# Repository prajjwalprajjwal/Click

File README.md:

# Clicker Project 🎮

Official repository for the Clicker handheld device ecosystem, encompassing production firmware, hardware schematics, PCB designs, CAD enclosure models, automated asset build pipelines, and browser-based WebUSB & WebSerial flashing tools.

---

## 📁 Repository Structure

```text
Click/
├── README.md                          <-- Master documentation and system overview
├── PROJECT_RULES.md                  <-- Protected subsystems, NVS rules & coding freeze
├── CHANGELOG.md                      <-- Comprehensive release history & architecture decisions
├── LICENSE                           <-- CC BY-NC-SA 4.0 International License
├── platformio.ini                    <-- PlatformIO configuration & automated build flags
├── build_release.bat                 <-- 1-Click Interactive firmware release packager
├── run_flasher.bat                   <-- 1-Click Localhost web flasher server runner
├── flash_device.bat                  <-- 1-Click Desktop CLI serial flasher
├── hardware/                         <-- Electrical schematics, 3D mechanical designs & production files
│   ├── Enclosure/                    <-- CAD enclosure assembly and 3D printable parts
│   │   ├── Assem4.SLDASM             <-- SolidWorks master enclosure assembly
│   │   ├── Click 4.SLDPRT            <-- SolidWorks case part model
│   │   ├── Click4_PCB.SLDPRT         <-- SolidWorks PCB envelope reference
│   │   └── STLs/                     <-- Production 3D-printable stereolithography meshes
│   │       ├── Case.STL              <-- Main device housing
│   │       ├── Case for Hook.STL     <-- Device housing with keychain/lanyard loop
│   │       ├── Back Plate w window.STL <-- Back cover with sensor/battery window
│   │       └── Back Plate w Hook.STL   <-- Back cover with keychain anchor
│   ├── PCB/                          <-- KiCad PCB manufacturing & CAD files
│   │   ├── Click4/                   <-- Active production PCBA (Raspberry Pi RP2354A)
│   │   │   ├── Click4.kicad_sch      <-- Production PCBA schematic
│   │   │   ├── Click4.kicad_pcb      <-- 4-layer impedance-controlled PCB layout
│   │   │   ├── Click4.step           <-- 3D MCAD export for enclosure fit check
│   │   │   └── production/           <-- JLCPCB Gerbers, drill files, BOM & CPL
│   │   ├── Click1/                   <-- Legacy prototype KiCad PCB & schematic (ESP32-WROOM-32E)
│   │   └── Resources/                <-- Edge cut DXFs, silkscreen vector artwork & graphics
│   ├── V4 Production Files/          <-- Ready-to-order manufacturing packages
│   │   ├── for JLCPCB.zip            <-- PCBA fabrication & assembly production archive
│   │   └── for JLC3DP.zip            <-- 3D printing enclosure fabrication archive
│   └── vector_designs.ai             <-- Vector graphics & enclosure laser engraving artwork
├── server/                           <-- Cloudflare Worker + D1 Serverless Leaderboard Backend
│   ├── worker.js                     <-- Edge API routes (/api/leaderboard, /api/sync, /api/user)
│   ├── schema.sql                    <-- D1 SQLite schema (devices, global_stats, sync_log)
│   ├── wrangler.toml                 <-- Cloudflare Worker deployment configuration
│   └── README.md                     <-- 3-minute zero-cost deployment guide
├── firmware/                         <-- Modular C++ embedded firmware
│   ├── assets/screens/               <-- 1-bit screen bitmaps & sprites (.png) + README.md
│   ├── scripts/
│   │   ├── pre_build_assets.py       <-- PlatformIO pre-build hook (auto-converts assets)
│   │   ├── convert_assets.py         <-- Converts PNGs to C PROGMEM bitmap headers
│   │   ├── flash.sh                  <-- Flashing utility for macOS / Linux
│   │   └── flash.bat                 <-- Flashing utility for Windows
│   └── src/                          <-- Application source code & applets
│       ├── main.cpp                  <-- Application entry point, serial protocol & registry
│       ├── system/                   <-- Core OS, drivers & power management (untouched by applets)
│       │   ├── Applet.h              <-- Base class interface for all applets
│       │   ├── OSManager.h / .cpp    <-- Applet scheduler & 3-stage sleep lifecycle
│       │   ├── PowerManager.h        <-- 12MHz XOSC sleep, __wfi(), double-click wake & I2C safety
│       │   ├── PinConfig.h           <-- Authoritative pin routing (RP2354A & ESP32)
│       │   ├── Display.h             <-- SSD1306 OLED singleton & 400kHz fast I2C
│       │   ├── InputManager.h / .cpp <-- Debounced button state machine & dual-key readers
│       │   ├── battery.hpp           <-- Non-linear LiPo curve, ADC filter & ETA6003 STAT
│       │   ├── WS2812.h              <-- PIO driver for 2x SK6812 RGB LEDs (GP11 DIN)
│       │   ├── SoundFX.h             <-- Non-blocking audio buzzer driver (GP27)
│       │   ├── HardwareDiagnostics.h / .cpp <-- Interactive & automated hardware test suite
│       │   └── device_info.hpp / .cpp<-- RP2354 Unique Board ID / eFuse MAC & custom bootscreen name
│       ├── applets/                  <-- Self-contained, modular games & apps
│       │   ├── clicker/              <-- Sisyphus uphill clicker game & physics engine
│       │   ├── timing_game/          <-- "Just 10 Seconds" accuracy timing game
│       │   ├── flappy_bird/          <-- Floppy Bird arcade obstacle game
│       │   ├── settings/             <-- Hardware status, voltage & device ID screen
│       │   └── screensaver/          <-- Snowfall particle animation on idle
│       ├── fonts/                    <-- Custom Adafruit GFX typography headers (Rajdhani)
│       ├── screens/                  <-- Legacy milestone overlay renderers
│       └── generated_assets/         <-- Auto-generated C bitmap headers
├── web_flasher/                      <-- WebUSB & WebSerial flasher, personalizer & leaderboard site
│   ├── index.html                    <-- Modern WebUSB/WebSerial application entry point
│   ├── flasher.html                  <-- Full-featured standalone flasher UI
│   ├── app.js                        <-- WebSerial engine, personalization & leaderboard sync
│   ├── rp2350-flash.js               <-- In-browser WebUSB Picoboot flasher & BOOTSEL flow
│   ├── rp2350-flash.css              <-- WebUSB installer & modal responsive styling
│   ├── style.css                     <-- Cyberpunk terminal responsive styling
│   ├── lib/                          <-- In-browser flashing drivers
│   │   ├── picoboot/                 <-- Native WebUSB Picoboot protocol driver (RP2350/RP2354)
│   │   └── uf2.js                    <-- Browser UF2 binary encoder/decoder
│   ├── flash-rp2350.bat / .sh        <-- Desktop Picotool update helper scripts
│   ├── manifest.json                 <-- WebSerial firmware manifest
│   ├── versions.json                 <-- Release catalog with hashes and download links
│   ├── releases/                     <-- Multi-version release archive (v0.1.1, v0.1.0, v0.0.1)
│   └── README.md                     <-- Web flasher guide, WebUSB/WebSerial docs & hosting
├── tools/                            <-- Build & developer utilities
│   ├── release/release_manager.py    <-- Interactive version bumper & binary packager
│   ├── flasher/                      <-- Flasher runner & desktop CLI scripts
│   │   ├── serve_flasher.py          <-- Zero-config HTTP server for web_flasher
│   │   └── flash_device.py           <-- Desktop serial flasher script
│   └── converters/                   <-- TTF font and image conversion scripts
└── docs/                             <-- Architectural specifications
    ├── hardware_and_pinouts.md       <-- Detailed pin profiles (RP2354A vs ESP32)
    ├── power_management_and_battery_architecture.md <-- Power optimization, battery fuel gauging & sleep currents
    ├── device_identification_and_leaderboard.md <-- Unique hardware ID & database schema
    └── leaderboard_architecture.md   <-- Cloudflare Worker API & score sync model
```

---

## ⚡ Hardware Platforms & Pin Profiles

Detailed technical schematics and electrical specifications can be found in [`docs/hardware_and_pinouts.md`](docs/hardware_and_pinouts.md).

> [!NOTE]
> **Active Hardware & Production Platforms**:
> - **Active Production Platform (Click 4 - RP2354A)**: Turnkey PCBA featuring the **Raspberry Pi RP2354A** MCU (Dual Cortex-M33, 512KB RAM, 4MB Flash). Features high-precision calibrated Li-Ion battery telemetry, 12MHz active sleep with $< 1\text{ mA}$ power consumption, dual SK6812 RGB LEDs, piezo sound, and PCF8563 RTC. Active default build environment: `env:rp2354`. Design files in `hardware/PCB/Click4/`.
> - **Legacy Prototype (Click 1 - ESP32-WROOM-32E)**: Hand-assembled prototype board maintained for backward compatibility under `env:esp32doit-devkit-v1`. Design files in `hardware/PCB/Click1/`.
> - **Power & Battery Deep-Dive**: For full architectural documentation on power management, battery discharge modeling, and silicon gotchas, read [**`docs/power_management_and_battery_architecture.md`**](docs/power_management_and_battery_architecture.md).

### Active Production Hardware Specs (Click 4: RP2354A)
- **Microcontroller**: Raspberry Pi RP2354A (Dual Cortex-M33 @ 48MHz, 512KB SRAM, 4MB on-chip Flash)
- **Display & RTC I2C Bus**: `CLICK_I2C = Wire1` (SDA = GP2, SCL = GP3, 400kHz Fast I2C)
- **User Inputs**: MODE = GP0 (Active LOW), ACTION = `BOOTSEL` / `QSPI_SS` (Active LOW)
- **Power & Battery**: STAT = GP1 (Active LOW charging from ETA6003 with 10k pullup), BAT_ADC = GP29 (ADC3 via 100k/100k divider)
- **Audio & Visual**: Buzzer = GP27 (via NPN BJT), RGB LEDs = GP11 (2× SK6812 DIN via PIO)
- **Power Management**: Same-Button Double-Click Wake protection (double-clicking the same key within 500ms), 3-stage sleep profile (8s dim, 15s display off, 30s deep sleep at 12MHz down-clocking $< 1\text{ mA}$), I2C bus preservation (0µA idle)

### Legacy Prototype Specs (Click 1: ESP32-WROOM-32E)
- **Microcontroller**: ESP32-WROOM-32E (Xtensa Dual-Core 240MHz, 4MB Flash)
- **Display I2C**: SDA = GPIO 21, SCL = GPIO 22 (400kHz Fast I2C)
- **User Inputs**: MODE = GPIO 14 (RTC ext0 wake), ACTION = GPIO 32 (RTC ext1 wake)
- **Power & Battery**: STAT = GPIO 33, BAT_ADC = GPIO 35 (100k/100k divider)
- **Sleep States**: Light sleep at 20s (OLED off, I2C pullups held), Deep sleep at 45s (RTC wakeup)

---

## 🕹️ Applet Ecosystem & Gameplay

The firmware features an event-driven `OSManager` hosting four built-in applets and an idle screensaver:

### 1. Sisyphus Clicker (Default Applet)
* **Theme**: Sisyphus rolling his eternal boulder up a steep mountain slope.
* **Dynamics**:
  * **Boulder Physics**: Smooth rotation and position tracking based on player clicks.
  * **Stamina & Fatigue**: Continuous clicking builds fatigue; stopping causes Sisyphus to catch his breath.
  * **Auditory Feedback**: 3 short beeps when the boulder rolls back downhill, with a gentle chime upon hitting bottom. Silent on startup into Sisyphus.
  * **Milestone Celebrations**: Overlay banners and RGB celebration pulses trigger on reaching milestone tiers.
  * **Persistence**: Dual-key NVS backup storage with checksum verification and wear-leveling.

### 2. Just Ten
* Precision stopwatch game challenging players to hold and release the button at exactly **10.0000 seconds**.
* Displays exact millisecond accuracy, tracks personal records, and flashes yellowish LEDs upon stopping.

### 3. Floppy Bird
* Real-time side-scrolling obstacle game featuring obstacle collision detection, velocity physics, and persistent high scores with red LED flash on game over.

### 4. Settings & System Applet
* Accessible by holding the **MODE** button.
* **Page 0 (SYSTEM)**: Shows live battery state (`[CHARGING]`, `[BATTERY]`, `[CHARGED]`), high-precision numerical voltage (`x.xxV`), and a graphical charge bar.
* **Page 1 (SYSTEM INFO)**: Center-aligned hardware telemetry displaying Firmware version, unique Device ID, and MCU specifications.

### 5. Snowfall Screensaver
* Ambient particle simulation that activates automatically when the device remains idle prior to entering sleep.

---

## 🎮 Controls & Navigation Guide

| Action | Control | Description |
|:---|:---|:---|
| **Cycle Applets** | `MODE` Button (Short Press) | Switch between **Clicker**, **Just Ten**, and **Floppy Bird** (click chime plays except before Sisyphus). |
| **Settings Menu** | `MODE` Button (Hold > 1s) | Toggle between the currently active applet and the **SYSTEM** settings screen. |
| **Toggle System Info** | `ACTION` Button (in Settings) | Toggle between Battery Telemetry (Page 0) and System Info (Page 1) screens. |
| **Primary Game Action** | `ACTION` Button (Short Press) | Push boulder in Sisyphus / Flap wings in Floppy Bird / Start & Stop in Just Ten. |
| **Wake from Sleep** | **Same-Button Double-Click** (two clicks on the same key within 500ms) | Wakes the device from low-power sleep back to the Sisyphus game (filters accidental single clicks & cross-key bumps). |
| **Factory Master Reset** | **Both Buttons Held** (> 4s) | Trigger master reset / clear NVS partitions and milestone progress. |

---

## 🛠️ Adding New Applets (Developer Guide)

The system firmware (`firmware/src/system/`) provides an isolated runtime environment. You or any contributor can add new games or micro-apps without touching, altering, or risking the core OS, sleep managers, or display drivers:

1. **Create an Applet Folder**: Create a directory in `firmware/src/applets/` (e.g., `firmware/src/applets/snake/`).
2. **Implement the `Applet` Interface**:
   ```cpp
   #pragma once
   #include "system/Applet.h"
   #include "system/Display.h"

   class SnakeApplet : public Applet {
   public:
       void init() override { /* Setup game state */ }
       void update() override { /* Real-time physics / tick loop */ }
       void draw() override { /* Draw frame on display */ }
       void cleanup() override { /* Teardown temporary state */ }
       void onActionClick() override { /* Handle ACTION button press */ }
   };
   ```
3. **Register in `firmware/src/main.cpp`**:
   ```cpp
   #include "applets/snake/SnakeApplet.h"
   SnakeApplet snakeApplet;

   // In setup():
   osManager.registerApplet(&snakeApplet);
   ```

All input debouncing, display clocking (400kHz Fast I2C), light sleep (15s), deep sleep (30s), and button wakeups continue working automatically in the background.

---

## 🚀 Building, Flashing & Updating

### 1. Web Flasher (Recommended)
* **Online**: Connect your device and visit [flashclick.uprajjwal.com.np](https://flashclick.uprajjwal.com.np).
  * **Click 4 (RP2354A)**: Hold the `ACTION` button (`BOOTSEL`) while plugging in USB-C, then click **Connect & Install Firmware** to flash directly via in-browser **WebUSB (Picoboot)**. No local drivers or utilities needed.
  * **Click 1 (ESP32)**: Connect via USB-C and flash directly via **WebSerial** using ESP Web Tools.
  * **Live Renaming & Community Boulder Sync**: Connect at runtime via WebSerial (115200 baud) to auto-detect device ID, personalize your custom bootscreen name, and sync clicks to the global leaderboard.
* **Local Server**: Double-click [`run_flasher.bat`](run_flasher.bat) or run:
  ```bash
  python tools/flasher/serve_flasher.py
  ```

### 2. Desktop Command-Line Flashing
* **Windows**: Run [`flash_device.bat`](flash_device.bat).
* **macOS / Linux**:
  ```bash
  chmod +x firmware/scripts/flash.sh
  ./firmware/scripts/flash.sh
  ```

### 3. Building via PlatformIO
The project uses PlatformIO with an automated asset compilation hook:
```bash
# Compile firmware for Click 4 (Raspberry Pi RP2354A - Default target)
pio run -e rp2354

# Compile with interactive Hardware Diagnostics Suite enabled
pio run -e rp2354-debug

# Compile for legacy prototype (ESP32-WROOM-32E)
pio run -e esp32doit-devkit-v1

# Upload directly over USB serial
pio run --target upload

# Open serial monitor (115200 baud)
pio device monitor -b 115200
```

### 4. Automated Asset Pipeline
Screen graphics placed in `firmware/assets/screens/` are converted to C headers before every compile:
```bash
python firmware/scripts/convert_assets.py
```

### 5. Official Release Packaging
To build an official release, bump semantic versions, and generate multi-target binary packages (UF2 + BIN):
```bash
# Windows
.\build_release.bat

# Python direct
python tools/release/release_manager.py
```

## 🌐 Community Leaderboard & Edge Cloud Architecture

The Click ecosystem features a fully connected, zero-maintenance, zero-cost ($0/month) serverless stack running on **Cloudflare Workers** and **Cloudflare D1 (Serverless SQLite)**:

```mermaid
flowchart LR
    DEV["🎮 Clicker Device\n(RP2354A / ESP32)"]
    WEB["💻 Web Flasher & Hub\n(flashclick.uprajjwal.com.np)"]
    CF["⚡ Cloudflare Worker\n(/api/sync, /api/leaderboard)"]
    D1[("🗄️ Cloudflare D1\n(SQLite at Edge)")]
    SITE["🏆 Community Leaderboard\n(click.uprajjwal.com.np)"]

    DEV <-->|"WebUSB (Flashing) / WebSerial (Telemetry)\nGET_ID / GET_STATS / SET_NAME"| WEB
    WEB -->|"POST /api/sync\n(Atomic delta push)"| CF
    CF <-->|"ACID SQLite Queries\nAnti-Cheat Validation"| D1
    SITE <-->|"GET /api/leaderboard\n(Edge-cached JSON)"| CF
```

### 1. The "Community Boulder" Mechanic 🪨
* Unlike isolated single-player games, every single click registered on any Clicker device contributes to the **Global Community Boulder**.
* When players connect to the Web Flasher and sync their device, their delta clicks are atomically added to `global_stats.total_boulder_clicks`.
* The live web interface visualizes the worldwide community progress as one shared mountain ascent.

### 2. Anti-Cheat & Physical Rate Limiting 🛡️
* The Cloudflare Worker enforces strict human-velocity checks on every sync request:
  * Delta clicks are validated against elapsed time between syncs (enforcing a physical maximum cap of ~15–20 clicks per second).
  * Excessive or impossible spikes are flagged and rejected, ensuring the Community Boulder and leaderboard rankings remain authentic.
  * Every sync transaction is immutably audited in the `sync_log` table with delta claims and hash signatures.

### 3. Device Personalization & Custom Bootscreen ✨
* Clickers are uniquely identified by their hardware silicon signature:
  * **Raspberry Pi RP2354A**: Permanent 16-character hex Unique Board ID queried via `pico_get_unique_board_id()` (e.g. `E6614104033C71BF`).
  * **ESP32-WROOM-32E**: Factory 12-character hex eFuse MAC address via `ESP.getEfuseMac()` (e.g. `3C71BF89A1B2`).
* Through the Web Flasher interface, players can set or personalize their custom owner name (e.g. `"Prajjwal's Click"`).
* Custom names can be baked into binary firmware via magic rodata signatures (`CLICK_NAME_MAGIC_PREFIX`) or saved persistently to NVS storage (`clicker_cfg` namespace).
* Upon boot, the physical SSD1306 OLED screen proudly renders the personalized owner name on the boot splash screen.

### 4. Interactive Serial Telemetry Protocol 🔌
The firmware exposes a high-speed telemetry interface over USB CDC serial (115200 baud) for browser-based synchronization:
* `GET_STATS` / `STATS` &rarr; Flushes active clicks to storage and returns structured JSON telemetry:
  `{"event":"stats","name":"CLICKER","chip_id":"...","clicks":35200,"floppy":42,"flappy":42,"just_ten":10.004,"uptime_hrs":12}`
* `SET_CLICKS <val>` &rarr; Sets lifetime click count and returns:
  `{"event":"clicks_updated","clicks":<val>}`
* `SET_STATS CLICKS=<n> FLOPPY=<n> JUST_TEN=<f>` (also accepts `FLAPPY=<n>`) &rarr; Restores all mini-game scores and returns:
  `{"event":"stats_restored","clicks":<n>,"floppy":<n>,"flappy":<n>,"just_ten":<f>}`
* `PING` &rarr; Returns heartbeat response: `{"event":"pong"}`

### 5. Live Links & Deployment
* **Live Community Leaderboard**: [click.uprajjwal.com.np](https://click.uprajjwal.com.np)
* **Web Flasher & Device Hub**: [flashclick.uprajjwal.com.np](https://flashclick.uprajjwal.com.np)
* **Backend Source & Deployment Guide**: [`server/README.md`](server/README.md)

---

## ⚖️ License

This project (Firmware, PCB schematics & layouts, 3D mechanical designs, and assets) is licensed under the **Creative Commons Attribution-NonCommercial-ShareAlike 4.0 International License ([CC BY-NC-SA 4.0](LICENSE))**.

* **Personal & Educational Use**: ✅ You are welcome to view, modify, download, and fabricate units for your personal, non-commercial use.
* **Commercial Manufacturing & Sale**: ❌ Manufacturing, assembling, packaging, or selling physical units, kits, PCBs, or parts for commercial gain is strictly prohibited without prior written permission from the author.
* See [LICENSE](LICENSE) for complete terms.

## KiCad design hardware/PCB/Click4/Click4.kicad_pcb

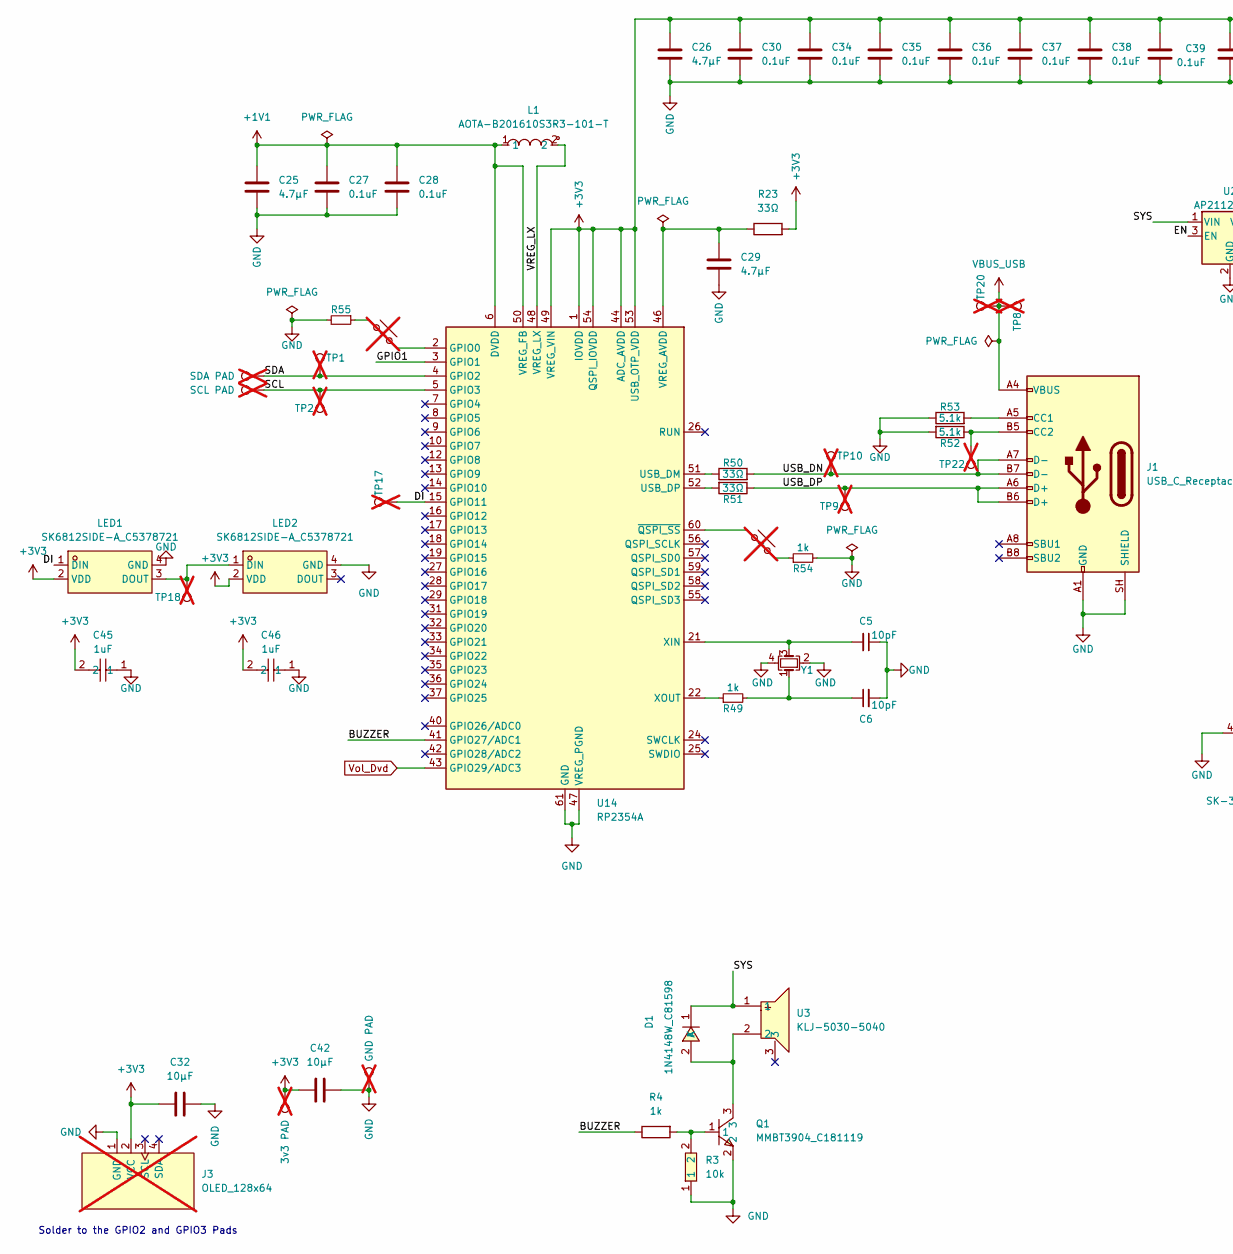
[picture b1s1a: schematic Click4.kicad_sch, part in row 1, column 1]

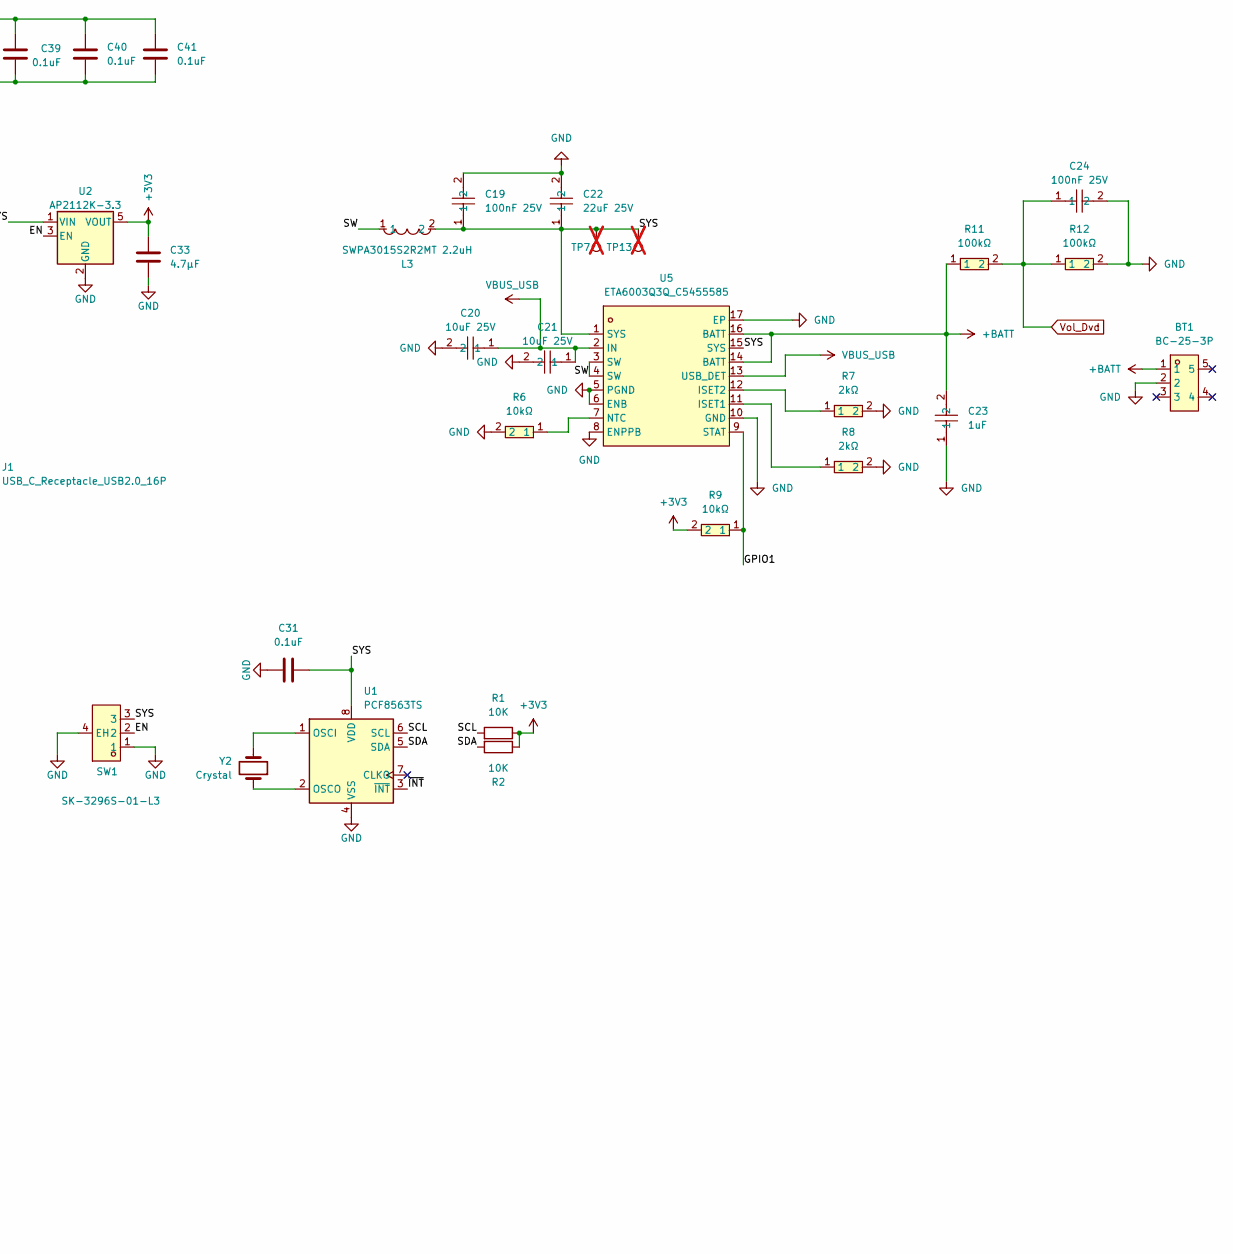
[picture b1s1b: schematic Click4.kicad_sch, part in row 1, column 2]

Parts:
BT1: BC-25-3P; CONN-SMD_BC-25-3P; MPN BC-25-3P; LCSC Part C707322
C5, C6: 10pF; C_0603_1608Metric; MPN CL10C100JB8NFNC
C19, C24: 100nF 25V; C_0603_1608Metric; MPN 0603B104K250NT; LCSC Part C694249
C20, C21: 10uF 25V; C_0805_2012Metric; MPN TCC0805X7R106K250FT; LCSC Part C48543594
C22: 22uF 25V; C_0805_2012Metric; MPN CGA0805X5R226M250MT; LCSC Part C6119899
C23, C45, C46: 1uF; C_0603_1608Metric; MPN TCC0603X7R105K250CT; LCSC Part C380328
C25, C26, C29: 4.7μF; C_0402_1005Metric; MPN GRM155D80E475ME47J; LCSC Part C23733
C27, C28, C30, C31, C34, C35, C36, C37, C38, C39, C40, C41: 0.1uF; C_0402_1005Metric; MPN CL05B104KA5NNNC; LCSC Part C1525
C32: 10μF; C_0402_1005Metric; MPN GRM155D80E475ME47J
C33: 4.7μF; C_0603_1608Metric; MPN CL10A475KO8NNNC; LCSC Part C19666
C42: 10μF; C_0402_1005Metric; MPN GRM155D80E475ME47J; LCSC Part C15525
D1: 1N4148W_C81598; SOD-123F_L2.7-W1.6-LS3.8-RD; MPN 1N4148W; LCSC Part C81598
J1: USB_C_Receptacle_USB2.0_16P; USB_C_Receptacle_G-Switch_GT-USB-7010ASV; LCSC Part C2765186
J3: OLED_128x64; not fitted
L1: AOTA-B201610S3R3-101-T; IND-SMD_L2.0-W1.6_AOTA-B201610S3R3-101-T; MPN AOTA-B201610S3R3-101-T; LCSC Part C42411119
L3: SWPA3015S2R2MT 2.2uH; IND-SMD_L3.0-W3.0; MPN SWPA3015S2R2MT; LCSC Part C43389
LED1, LED2: SK6812SIDE-A_C5378721; LED-SMD_4P-L4.0-W1.6-L; MPN SK6812SIDE-A; LCSC Part C5378721
Q1: MMBT3904_C181119; SOT-23-3; MPN MMBT3904; LCSC Part C181119
R1, R2: 10K; R_0402_1005Metric; LCSC Part C25744
R3: 10k; R_0603_1608Metric; MPN 0603WAF1002T5E; LCSC Part C25804
R4, R49, R54, R55: 1k; R_0603_1608Metric; MPN RT0603FRE101KL; LCSC Part C21190
R6, R9: 10kΩ; R_0603_1608Metric; MPN 0603WAF1002T5E; LCSC Part C25804
R7, R8: 2kΩ; R_0603_1608Metric; MPN RC0603FR-072KL; LCSC Part C105576
R11, R12: 100kΩ; R_0603_1608Metric; MPN 0603WAF1003T5E; LCSC Part C25803
R23, R50, R51: 33Ω; R_0402_1005Metric; MPN RC0402FR-0733RL; LCSC Part C138002
R52, R53: 5.1k; R_0402_1005Metric; MPN RC0402FR-075K1L; LCSC Part C25905
S1, S2: MX_PCB_1.00u; not fitted
SW1: SK-3296S-01-L3; SW-SMD_SK-3296S-01-L3; MPN SK-3296S-01-L3; LCSC Part C319019
TP1, TP2, TP7, TP8, TP9, TP10, TP13, TP17, TP18, TP20, TP22: TestPoint; TestPoint_Pad_D1.0mm; not fitted
TP3: SDA PAD; TestPoint_Pad_D2.0mm; not fitted
TP4: SCL PAD; TestPoint_Pad_D2.0mm; not fitted
TP5: 3v3 PAD; TestPoint_Pad_D2.0mm; not fitted
TP6: GND PAD; TestPoint_Pad_D2.0mm; not fitted
U1: PCF8563TS; MSOP-8_3x3mm_P0.65mm; LCSC Part C27397
U2: AP2112K-3.3; SOT-23-5; MPN AP2112K-3.3TRG1
U3: KLJ-5030-5040; BUZ-SMD_3P-L5.0-W5.0-BL; MPN KLJ-5030-5040; LCSC Part C18186311
U5: ETA6003Q3Q_C5455585; QFN-16_L3.0-W3.0-P0.50-TL-EP1.7-2; MPN ETA6003Q3Q; LCSC Part C5455585
U14: RP2354A; QFN-60-1EP_7x7mm_P0.4mm_EP3.4x3.4mm; MPN SC1511(13)-A4
Y1: Crystal; Crystal_SMD_3225-4Pin_3.2x2.5mm; MPN ABM8-272-T3; LCSC Part C20625731
Y2: Crystal; Crystal_SMD_3215-2Pin_3.2x1.5mm; LCSC Part C97604

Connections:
+1V1: C25.1, C27.2, C28.2, L1.1, U14.6 (DVDD), U14.23 (DVDD), U14.39 (DVDD), U14.50 (VREG_FB)
+3V3: C26.1, C30.2, C32.1, C33.1, C34.2, C35.2, C36.2, C37.2, C38.2, C39.2, C40.2, C41.2, C42.1, C45.2, C46.2, J3.2 (VCC), LED1.2 (VDD), LED2.2 (VDD), R1.1, R2.1, R9.2, R23.2, TP5.1 (1_1), U2.5 (VOUT), U14.1 (IOVDD), U14.11 (IOVDD), U14.20 (IOVDD), U14.30 (IOVDD), U14.38 (IOVDD), U14.44 (ADC_AVDD), U14.45 (IOVDD), U14.49 (VREG_VIN), U14.53 (USB_OTP_VDD), U14.54 (QSPI_IOVDD)
+BATT: BT1.1, C23.2, R11.1, U5.14 (BATT), U5.16 (BATT)
/BUZZER: R4.1, U14.41 (GPIO27/ADC1)
/DI: LED1.1 (DIN), TP17.1 (1_1), U14.15 (GPIO11)
/EN: SW1.2, U2.3 (EN)
/GPIO1: R9.1, U5.9 (STAT), U14.3 (GPIO1)
/SCL: R1.2, TP2.1 (1_1), TP4.1 (1_1), U1.6 (SCL), U14.5 (GPIO3)
/SDA: R2.2, TP1.1 (1_1), TP3.1 (1_1), U1.5 (SDA), U14.4 (GPIO2)
/SW: L3.1, U5.3 (SW), U5.4 (SW)
/SYS: C19.1, C22.1, C31.1, D1.1 (K), L3.2, SW1.3, TP7.1 (1_1), TP13.1 (1_1), U1.8 (VDD), U2.1 (VIN), U3.1, U5.1 (SYS), U5.15 (SYS)
/USB_DN: J1.A7 (D-), J1.B7 (D-), R50.2, TP10.1 (1_1)
/USB_DP: J1.A6 (D+), J1.B6 (D+), R51.1, TP9.1 (1_1)
/VREG_LX: L1.2, U14.48 (VREG_LX)
/~INT: U1.3 (~INT)
GND: BT1.2, C5.1, C6.2, C19.2, C20.2, C21.2, C22.2, C23.1, C24.2, C25.2, C26.2, C27.1, C28.1, C29.2, C30.1, C31.2, C32.2, C33.2, C34.1, C35.1, C36.1, C37.1, C38.1, C39.1, C40.1, C41.1, C42.2, C45.1, C46.1, J1.A1 (GND), J1.A12 (GND), J1.B1 (GND), J1.B12 (GND), J1.SH (SHIELD), J3.1 (GND), LED1.4 (GND), LED2.4 (GND), Q1.2, R3.1, R6.2, R7.2, R8.2, R12.2, R52.2, R53.1, R54.2, R55.2, SW1.1, SW1.4 (EH), TP6.1 (1_1), U1.4 (VSS), U2.2 (GND), U5.5 (PGND), U5.6 (ENB), U5.8 (ENPPB), U5.10 (GND), U5.17 (EP), U14.47 (VREG_PGND), U14.61 (GND), Y1.2, Y1.4
unnamed: C6.1, R49.2, Y1.1
unnamed: D1.2 (A), Q1.3, U3.2
unnamed: J1.A5 (CC1), R53.2
unnamed: J1.B5 (CC2), R52.1, TP22.1 (1_1)
unnamed: LED1.3 (DOUT), LED2.1 (DIN), TP18.1 (1_1)
unnamed: Q1.1, R3.2, R4.2
unnamed: R54.1, S2.2
unnamed: R55.1, S1.1
unnamed: U1.1 (OSCI), Y2.2
unnamed: U1.2 (OSCO), Y2.1
unnamed: R8.1, U5.11 (ISET1)
unnamed: R7.1, U5.12 (ISET2)
unnamed: R6.1, U5.7 (NTC)
unnamed: S1.2, U14.2 (GPIO0)
unnamed: R50.1, U14.51 (USB_DM)
unnamed: R51.2, U14.52 (USB_DP)
unnamed: C29.1, R23.1, U14.46 (VREG_AVDD)
unnamed: C5.2, U14.21 (XIN), Y1.3
unnamed: R49.1, U14.22 (XOUT)
unnamed: S2.1, U14.60 (~QSPI_SS)
VBUS_USB: C20.1, C21.1, J1.A4 (VBUS), J1.A9 (VBUS), J1.B4 (VBUS), J1.B9 (VBUS), TP8.1 (1_1), TP20.1 (1_1), U5.2 (IN), U5.13 (USB_DET)
Vol_Dvd: C24.1, R11.2, R12.1, U14.43 (GPIO29/ADC3)

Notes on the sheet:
Solder to the GPIO2 and GPIO3 Pads

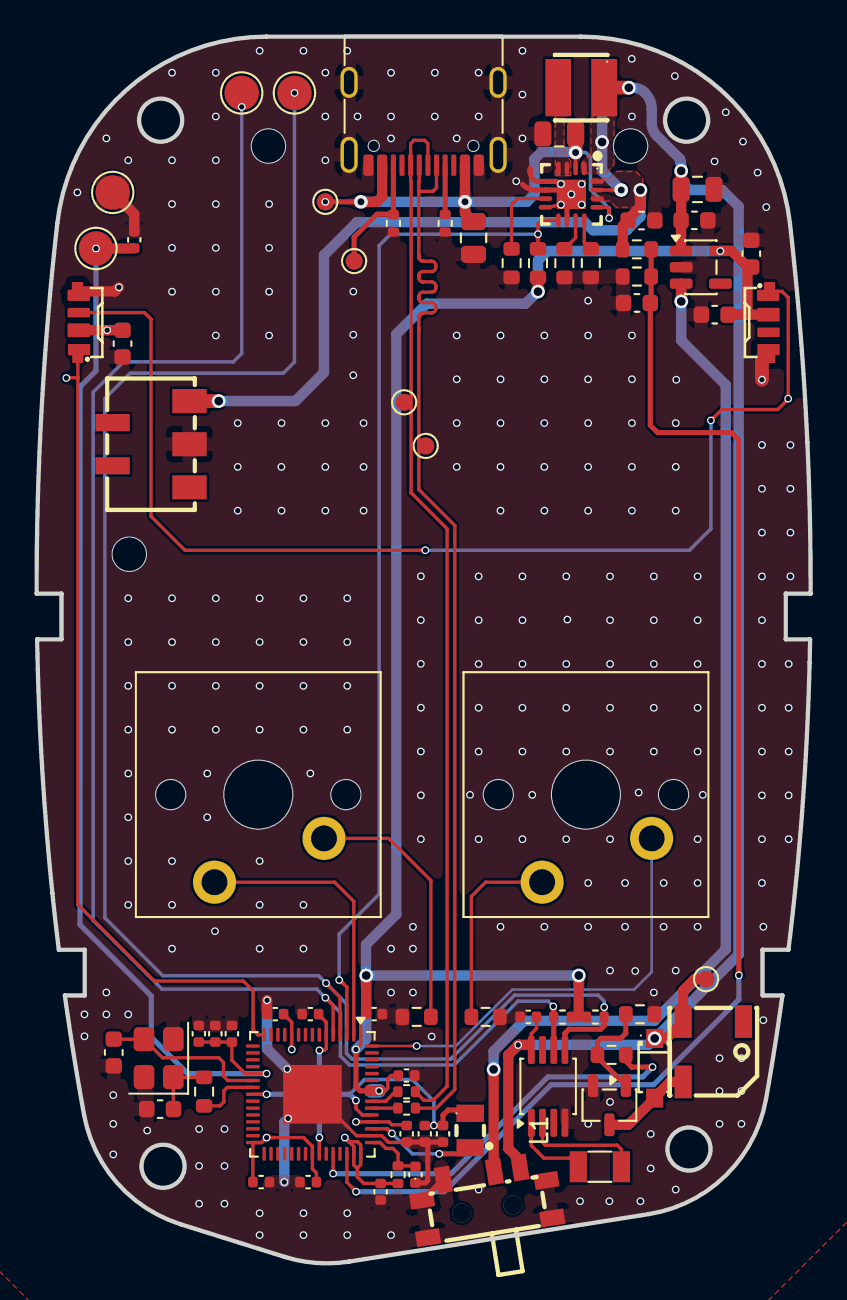
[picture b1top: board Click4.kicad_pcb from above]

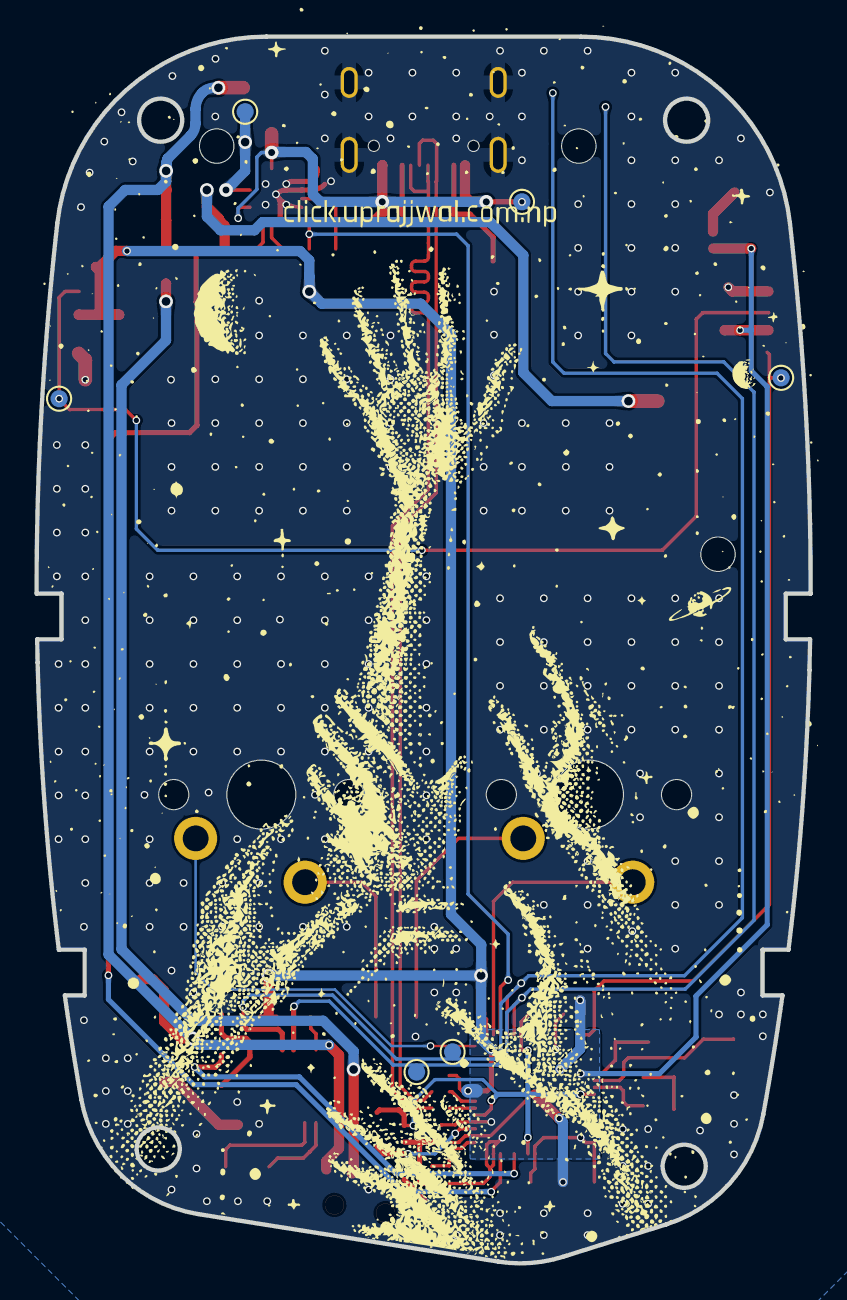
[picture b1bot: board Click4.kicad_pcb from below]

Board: 2 copper layers, 44.9 x 71.1 mm, 78 parts (6 on the bottom side), 37 nets.

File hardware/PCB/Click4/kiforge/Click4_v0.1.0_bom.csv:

"Reference","Value","Footprint","Manufacturer","MPN","ID","Description","QUANTITY","DNP"
"BT1","BC-25-3P","easyeda2kicad:CONN-SMD_BC-25-3P","韩国韩荣","BC-25-3P","","","1",""
"C5,C6","10pF","Capacitor_SMD:C_0603_1608Metric","","CL10C100JB8NFNC","","","2",""
"C19,C24","100nF 25V","Capacitor_SMD:C_0603_1608Metric","FH(风华)","0603B104K250NT","","","2",""
"C20,C21","10uF 25V","Capacitor_SMD:C_0805_2012Metric","CCTC(三环)","TCC0805X7R106K250FT","","","2",""
"C22","22uF 25V","Capacitor_SMD:C_0805_2012Metric","HRE(芯声)","CGA0805X5R226M250MT","","","1",""
"C23,C45,C46","1uF","Capacitor_SMD:C_0603_1608Metric","CCTC(三环)","TCC0603X7R105K250CT","","","3",""
"C25,C26,C29","4.7μF","Capacitor_SMD:C_0402_1005Metric","","GRM155D80E475ME47J","","Unpolarized capacitor","3",""
"C27,C28,C30,C31,C34,C35,C36,C37,C38,C39,C40,C41","0.1uF","Capacitor_SMD:C_0402_1005Metric","","CL05B104KA5NNNC","","","12",""
"C32,C42","10μF","Capacitor_SMD:C_0402_1005Metric","","GRM155D80E475ME47J","","Unpolarized capacitor","2",""
"C33","4.7μF","Capacitor_SMD:C_0603_1608Metric","","CL10A475KO8NNNC","","Unpolarized capacitor","1",""
"D1","1N4148W_C81598","easyeda2kicad:SOD-123F_L2.7-W1.6-LS3.8-RD","ST(先科)","1N4148W","","1N4148W","1",""
"J1","USB_C_Receptacle_USB2.0_16P","Connector_USB:USB_C_Receptacle_G-Switch_GT-USB-7010ASV","","","","USB 2.0-only 16P Type-C Receptacle connector","1",""
"L1","AOTA-B201610S3R3-101-T","easyeda2kicad:IND-SMD_L2.0-W1.6_AOTA-B201610S3R3-101-T","ABRACON","AOTA-B201610S3R3-101-T","","","1",""
"L3","SWPA3015S2R2MT 2.2uH","easyeda2kicad:IND-SMD_L3.0-W3.0","Sunlord(顺络)","SWPA3015S2R2MT","","SWPA3015S2R2MT","1",""
"LED1,LED2","SK6812SIDE-A_C5378721","easyeda2kicad:LED-SMD_4P-L4.0-W1.6-L","OPSCO(欧思科)","SK6812SIDE-A","","","2",""
"Q1","MMBT3904_C181119","Package_TO_SOT_SMD:SOT-23-3","Hottech(合科泰)","MMBT3904","","","1",""
"R1,R2","10K","Resistor_SMD:R_0402_1005Metric","","","","Resistor","2",""
"R3","10k","Resistor_SMD:R_0603_1608Metric","UNI-ROYAL(厚声)","0603WAF1002T5E","","10KΩ (1002) ±1%","1",""
"R4,R49,R54,R55","1k","Resistor_SMD:R_0603_1608Metric","","RT0603FRE101KL","","Resistor","4",""
"R6,R9","10kΩ","Resistor_SMD:R_0603_1608Metric","UNI-ROYAL(厚声)","0603WAF1002T5E","","10KΩ (1002) ±1%","2",""
"R7,R8","2kΩ","Resistor_SMD:R_0603_1608Metric","YAGEO(国巨)","RC0603FR-072KL","","","2",""
"R11,R12","100kΩ","Resistor_SMD:R_0603_1608Metric","UNI-ROYAL(厚声)","0603WAF1003T5E","","100KΩ (1003) ±1%","2",""
"R23,R50,R51","33Ω","Resistor_SMD:R_0402_1005Metric","","RC0402FR-0733RL","","Resistor","3",""
"R52,R53","5.1k","Resistor_SMD:R_0402_1005Metric","","RC0402FR-075K1L","","Resistor","2",""
"SW1","SK-3296S-01-L3","easyeda2kicad:SW-SMD_SK-3296S-01-L3","XKB Connection(中国星坤)","SK-3296S-01-L3","","","1",""
"U1","PCF8563TS","Package_SO:MSOP-8_3x3mm_P0.65mm","","","","Realtime Clock/Calendar I2C Interface, TSSOP-8","1",""
"U2","AP2112K-3.3","Package_TO_SOT_SMD:SOT-23-5","","AP2112K-3.3TRG1","","","1",""
"U3","KLJ-5030-5040","easyeda2kicad:BUZ-SMD_3P-L5.0-W5.0-BL","KELIKING(凯丽金)","KLJ-5030-5040","","","1",""
"U5","ETA6003Q3Q_C5455585","easyeda2kicad:QFN-16_L3.0-W3.0-P0.50-TL-EP1.7-2","ETA(钰泰)","ETA6003Q3Q","","","1",""
"U14","RP2354A","Package_DFN_QFN:QFN-60-1EP_7x7mm_P0.4mm_EP3.4x3.4mm","","SC1511(13)-A4","","A microcontroller by Raspberry Pi, dual CPU architecture (ARM Cortex-M33 / RISC-V Hazard3), 150MHz, 2MB flash, 520KB SRAM, 12 PIO state machines, VQFN-60","1",""
"Y1","Crystal","Crystal:Crystal_SMD_3225-4Pin_3.2x2.5mm","","ABM8-272-T3","","","1",""
"Y2","Crystal","Crystal:Crystal_SMD_3215-2Pin_3.2x1.5mm","","","","Two pin crystal","1",""

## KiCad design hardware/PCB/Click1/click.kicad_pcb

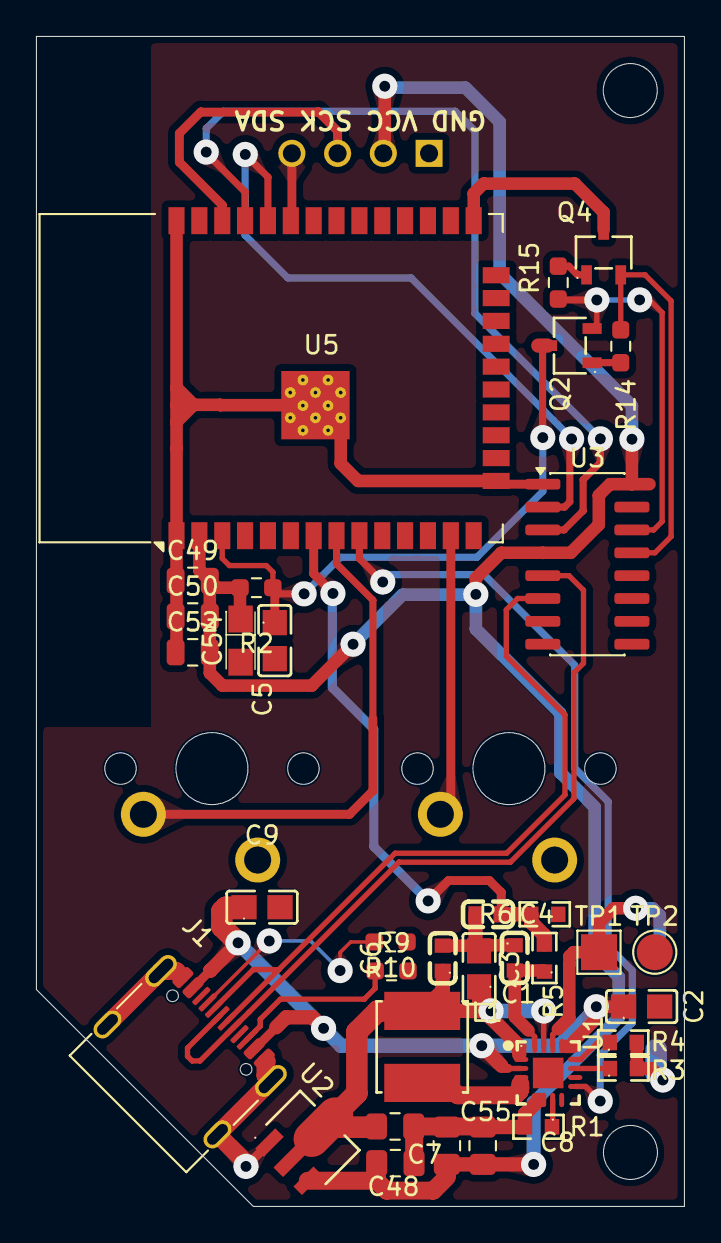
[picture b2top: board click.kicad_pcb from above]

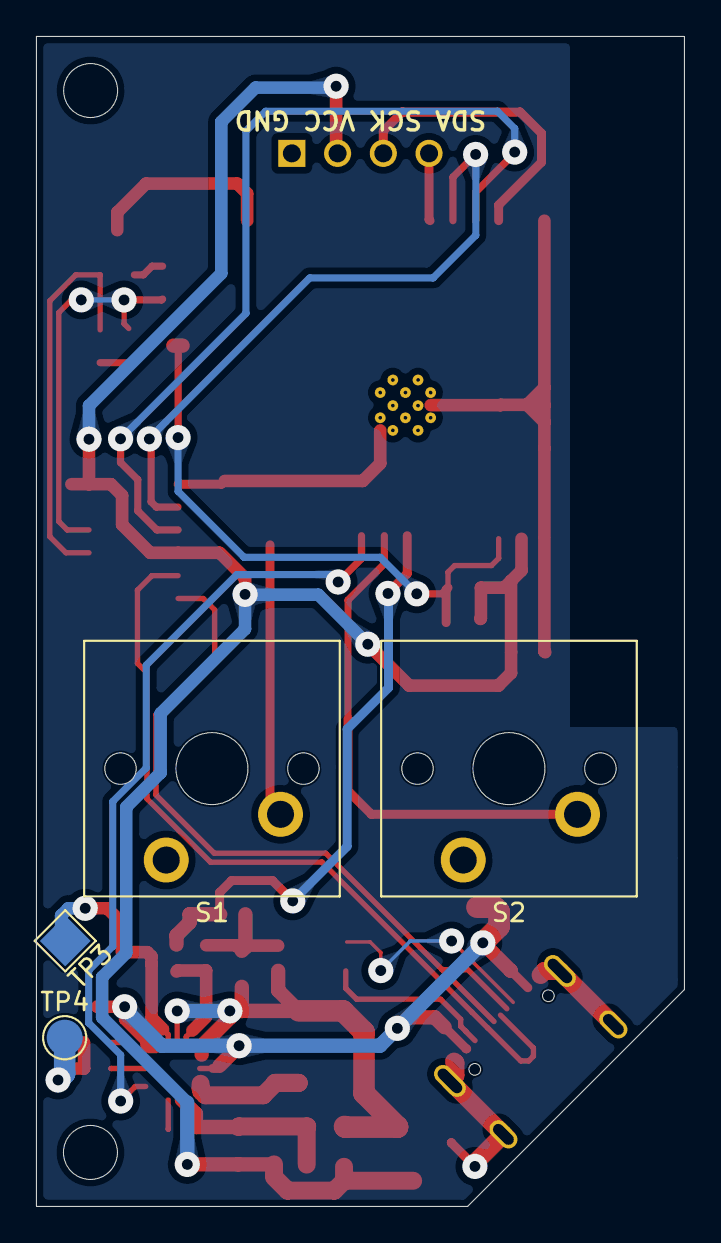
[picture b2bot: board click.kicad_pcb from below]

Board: 2 copper layers, 36.0 x 65.0 mm, 40 parts (5 on the bottom side), 27 nets.

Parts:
C1: 1uF; C0603
C2, C9: 10uF 25V; C0805
C3: 22uF 25V; C0805
C4, C6: 100nF 25V; C0603
C5: CL21B105KBFNNNE; C0805
C7, C8: 22uF X5R 25V; C_0805_2012Metric_Pad1.18x1.45mm_HandSolder
C48, C55: 100n; C_0805_2012Metric_Pad1.18x1.45mm_HandSolder
C49: 33pF C0G 50V; C_0805_2012Metric
C50: 100nF X7R 50V; C_0805_2012Metric
C52: 22uF X5R 25V; C_0805_2012Metric
C54: TAN 100uF 6.3V; CASE-A_3216
J1: USB_C_Receptacle_USB2.0_16P; USB_C_Receptacle_G-Switch_GT-USB-7010ASV
J2: OLED_128x64
L1: 2.2uH 3.2A; IND-SMD_L5.0-W5.0
Q2, Q4: MMBT3904_C181119; SOT-23-3_L2.9-W1.6-P1.90-LS2.8-BR
R1: 10kΩ; R0603
R2: 10K 1%; R_0603_1608Metric_Pad0.98x0.95mm_HandSolder
R3, R4: 2kΩ; R0603
R5, R6: 100kΩ; R0603
R9, R10: 5k1; R_0603_1608Metric_Pad0.98x0.95mm_HandSolder
R14, R15: 10k; R_0603_1608Metric_Pad0.98x0.95mm_HandSolder
S1, S2: MX_PCB_1.00u
TP1, TP3: TestPoint; TestPoint_Pad_2.0x2.0mm
TP2, TP4: TestPoint; TestPoint_Pad_D2.0mm
U1: ETA6003Q3Q_C5455585; QFN-16_L3.0-W3.0-P0.50-TL-EP1.7-2
U2: HT7833; SOT-89_L4.5-W2.5-P1.50-LS4.2-BR
U3: CH340C; SOIC-16_3.9x9.9mm_P1.27mm
U5: ESP32-WROOM-32E; ESP32-WROOM-32D

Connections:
+3V3: C8.2, C48.1, C49.2, C50.2, C52.2, C54.1, C55.1, J2.2 (VCC), R2.2, U2.3 (OUT), U3.4 (V3), U3.16 (VCC), U5.2 (VDD)
+BATT: C1.2, R5.1, TP1.1 (1_1), TP3.1 (1_1), U1.14 (BATT), U1.16 (BATT)
/D+: J1.A6 (D+), J1.B6 (D+), U3.5 (UD+)
/D-: J1.A7 (D-), J1.B7 (D-), U3.6 (UD-)
/DTR: Q4.2, R14.1, U3.13 (~DTR)
/EN: C5.1, Q2.3, R2.1, U5.3 (EN)
/IO0: Q4.3, U5.25 (IO0)
/RTS: Q2.2, R15.1, U3.14 (~RTS)
/RXD: U3.3 (RXD), U5.35 (TXD0/IO1)
/STAT: U1.9 (STAT), U5.9 (IO33)
/TXD: U3.2 (TXD), U5.34 (RXD0/IO3)
ETA_VOUT_PWR: C3.1, C6.1, C7.2, L1.2, U1.1 (SYS), U1.15 (SYS), U2.2 (IN)
GND: C1.1, C2.2, C3.2, C4.2, C5.2, C6.2, C7.1, C8.1, C9.2, C48.2, C49.1, C50.1, C52.1, C54.2, C55.2, J1.A1 (GND), J1.A12 (GND), J1.B1 (GND), J1.B12 (GND), J1.SH (SHIELD), J2.1 (GND), R1.2, R3.2, R4.2, R6.2, R9.1, R10.1, S1.2, S2.2, TP2.1 (1_1), TP4.1 (1_1), U1.5 (PGND), U1.6 (ENB), U1.8 (ENPPB), U1.10 (GND), U1.17 (EP), U2.1 (GND), U3.1 (GND), U5.1 (GND), U5.15 (GND), U5.38 (GND), U5.39 (GND)
unnamed: J1.A5 (CC1), R10.2
unnamed: J1.B5 (CC2), R9.2
unnamed: J2.3 (SCL), U5.36 (IO22)
unnamed: J2.4 (SDA), U5.33 (IO21)
unnamed: L1.1, U1.3 (SW), U1.4 (SW)
unnamed: Q2.1, R14.2
unnamed: Q4.1, R15.2
unnamed: R3.1, U1.11 (ISET1)
unnamed: R4.1, U1.12 (ISET2)
unnamed: R1.1, U1.7 (NTC)
unnamed: S1.1, U5.13 (IO14)
unnamed: S2.1, U5.8 (IO32)
VBUS_USB: C2.1, C9.1, J1.A4 (VBUS), J1.A9 (VBUS), J1.B4 (VBUS), J1.B9 (VBUS), U1.2 (IN), U1.13 (USB_DET)
Vol_Dvd: C4.1, R5.2, R6.1, U5.7 (IO35)
